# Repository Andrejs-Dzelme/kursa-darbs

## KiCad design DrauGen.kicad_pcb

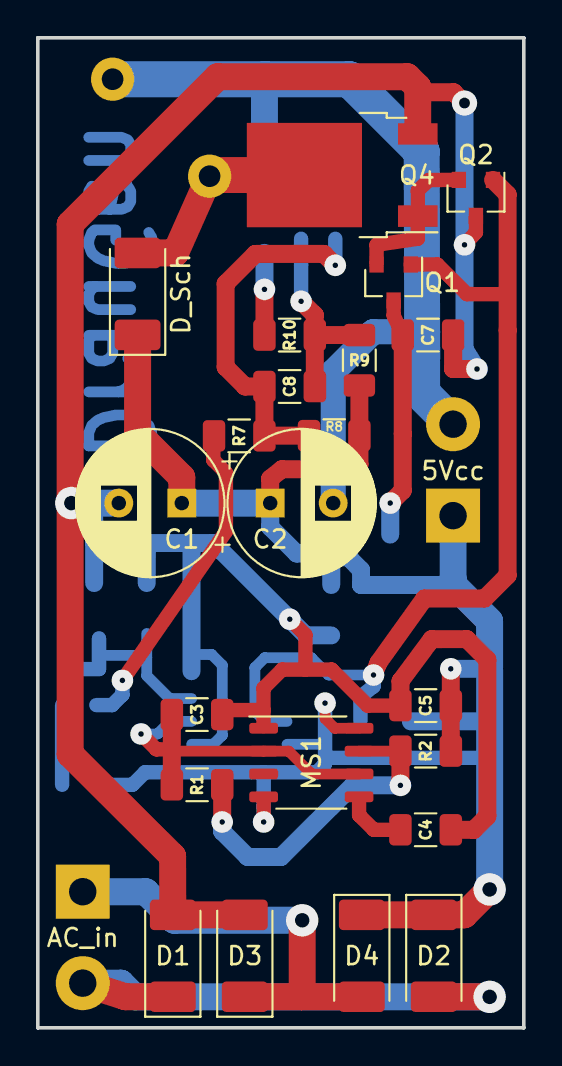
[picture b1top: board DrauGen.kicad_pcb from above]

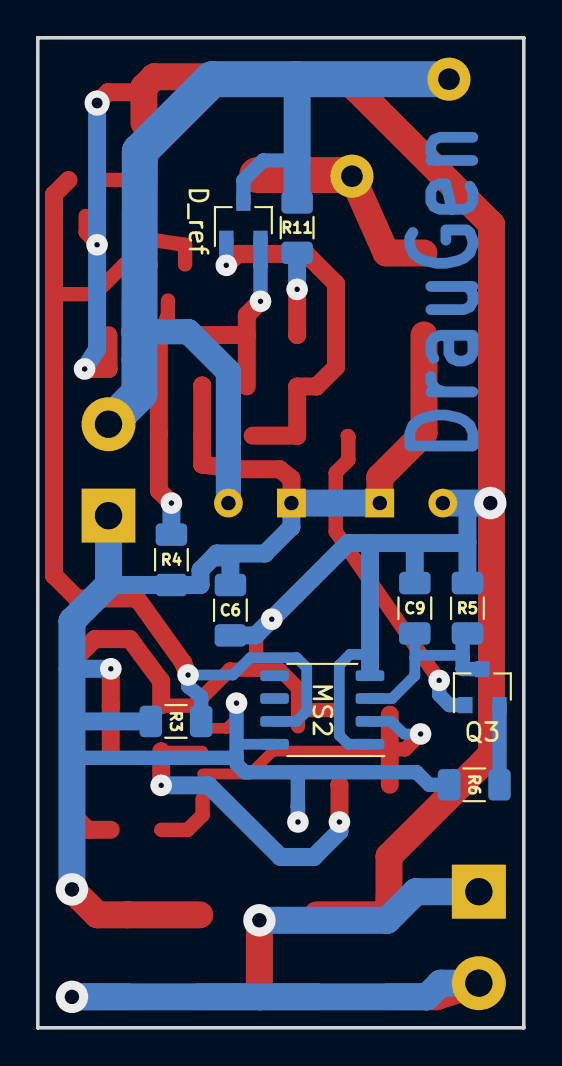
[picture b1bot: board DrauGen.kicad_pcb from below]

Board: 2 copper layers, 27.0 x 55.0 mm, 35 parts (10 on the bottom side), 18 nets.

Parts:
5Vcc: Screw_Terminal_01x02; TerminalBlock_bornier-2_P5.08mm
AC_in: Screw_Terminal_01x02; TerminalBlock_bornier-2_P5.08mm
C1, C2: 1000u; CP_Radial_D8.0mm_P3.50mm
C3: 470p; C_1206_3216Metric
C4, C5, C6, C9: 0.1u; C_1206_3216Metric
C7, C8: 47n; C_1206_3216Metric
D1, D2, D3, D4: D_Schottky; D_2010_5025Metric_Castellated
D5: D_Sch; D_2010_5025Metric_Castellated
D_ref: TL431DBZ; SOT-23
L1: 340uH; L_Axial_L20.3mm_D12.7mm_P7.62mm_Vertical_Vishay_IHA-201
MS1: NE555; NE_555_3.9x4.9mm_P1.27mm_EP2.41x3.1mm
MS2: LM311; NE_555_3.9x4.9mm_P1.27mm_EP2.41x3.1mm
Q1: BC817-40LT1G; SOT-23
Q2, Q3: BC807-40LT1G; SOT-23
Q4: FDD5690; TO-252-2
R1: 24k; C_1206_3216Metric
R2, R3: 1k; C_1206_3216Metric
R4: 100R; C_1206_3216Metric
R5: 47k; C_1206_3216Metric
R6, R8: 10k; C_1206_3216Metric
R7: 100k; C_1206_3216Metric
R9: 39k; C_1206_3216Metric
R10: 56k? (15k); C_1206_3216Metric
R11: 56k? (22k); C_1206_3216Metric

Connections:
GND: C1.2, C3.2, C4.2, C5.1, C6.1, C7.1, C9.2, D1.2, D3.2, MS1.1, MS2.1, MS2.4, Q2.2, Q4.3, R5.2
unnamed: 5Vcc.1, C1.1, C2.1, C5.2, C6.2, D2.1, D4.1, D5.1, MS1.4, MS1.8, MS2.8, R2.1, R3.1, R4.2, R6.1, R8.1, R9.2
unnamed: 5Vcc.2, C2.2, D_ref.2, L1.2, R11.2
unnamed: C3.1, MS1.2, MS1.6, MS2.2, R1.2
unnamed: C4.1, MS1.5
unnamed: C7.2, Q1.2, R4.1
unnamed: C8.1, D_ref.3, R9.1, R10.2
unnamed: C8.2, D_ref.1, R7.1, R8.2
unnamed: C9.1, MS2.3, Q3.2, R5.1
unnamed: AC_in.2, D1.1, D2.2
unnamed: AC_in.1, D3.1, D4.2
unnamed: D5.2, L1.1, Q4.2
unnamed: MS2.7, Q1.1, Q2.1, R3.2
unnamed: Q1.3, Q2.3, Q4.1
unnamed: Q3.1, R7.2
unnamed: Q3.3, R6.2
unnamed: MS1.7, R1.1, R2.2
unnamed: R10.1, R11.1

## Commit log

2020-06-10 DrauGen update to test GitHub Repo
